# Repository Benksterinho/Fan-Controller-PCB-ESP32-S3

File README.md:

# JumboNAS Fan Controller PCB (ESP32-S3, Rev A)

This repository contains the hardware design and supporting documentation for a maker-friendly 4-wire PWM fan controller board built around ESP32-S3.

The PCB is intended for projects that need to power and control a standard 12 V PC fan, read tach feedback, and optionally show status on an SPI display, with room for future telemetry and expansion.

## What This Board Is For

- Controlling one 12 V 4-wire PWM fan from an ESP32-S3.
- Reading fan tach pulses for RPM measurement.
- Running standalone logic in CircuitPython on ESP32-S3.
- Driving an external ST7789 SPI display header.
- Exposing safe optional GPIOs through an expansion header.

Typical use cases:

- DIY NAS or homelab cooling controller.
- Smart enclosure or cabinet fan controller.
- General embedded fan-control bring-up platform.

## Hardware Overview

- Input power: 19-24 V DC recommended.
- Reverse polarity and surge protection at board input.
- 12 V rail: K7812 SIP module regulator.
- 3.3 V rail: K7803 SIP module regulator.
- Controller: ESP32-S3-WROOM-1-N16R8.
- Fan interface: Intel-style 4-pin PWM fan header.
- Programming/debug: external 1x6 UART header.

Input note:

- 19-24 V is the supported operating range for Rev A.
- 17-18 V may work in some conditions but is not guaranteed with the current Schottky protection stage.

## Project Status

Rev A is an actively developed hardware revision focused on first-pass manufacturability and bring-up reliability.

Current priorities:

- Keep BOM practical for PCBWay/LCSC assembly.
- Keep board size within cost-efficient limits (target under 99 x 99 mm).
- Use conservative, proven power-stage choices for a first hardware spin.

## Repository Layout

- [docs](docs): design rationale, requirements, BOM, sourcing, and build notes.
- [docs/sheet-specs](docs/sheet-specs): per-subsheet intent and signal definitions.
- [hardware/kicad/fan_controller_revA](hardware/kicad/fan_controller_revA): KiCad project files for Rev A.
- [firmware](firmware): reserved area for CircuitPython firmware and bring-up utilities.

## If You Want To Build One

1. Read [docs/requirements.md](docs/requirements.md) for scope and constraints.
2. Read [docs/architecture.md](docs/architecture.md) for system-level decisions.
3. Review [docs/bom-revA.csv](docs/bom-revA.csv) and [docs/bom-revA-status.md](docs/bom-revA-status.md).
4. Open the KiCad project in [hardware/kicad/fan_controller_revA](hardware/kicad/fan_controller_revA).
5. Follow manufacturing notes in [docs/pcbway-assembly.md](docs/pcbway-assembly.md).

## Key Docs

- [docs/architecture.md](docs/architecture.md)
- [docs/requirements.md](docs/requirements.md)
- [docs/current-budget.md](docs/current-budget.md)
- [docs/schematic-plan.md](docs/schematic-plan.md)
- [docs/gpio-map.md](docs/gpio-map.md)
- [docs/bom-revA.csv](docs/bom-revA.csv)
- [docs/bom-revA-status.md](docs/bom-revA-status.md)
- [docs/sourcing-checklist.md](docs/sourcing-checklist.md)
- [docs/pcbway-assembly.md](docs/pcbway-assembly.md)

## Safety And Scope

This is a low-voltage maker hardware project and is provided as-is. Validate thermal behavior, fan startup behavior, and input transient behavior in your own enclosure and power environment before unattended use.

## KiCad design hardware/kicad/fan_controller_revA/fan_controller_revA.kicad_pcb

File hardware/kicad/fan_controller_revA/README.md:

# Fan Controller Rev A - KiCad Notes

Generated schematic files were removed. This folder now serves as the capture guide and naming reference.

## Files

- howto_subsheets/ (step-by-step capture guides)
- pcb_layout/ (subsheet-specific PCB Editor placement and routing guides)
- README.md (capture order and shared net naming)

## Capture Order

1. InputProtection
2. Power12V
3. Power3V3
4. ESP32S3Core
5. Fan4Wire
6. DisplayHeader_ST7789
7. ExternalProgrammingHeader
8. TestPoints
9. OptionalExpansionHeader

## Global Net Names To Reuse

- VIN_PROTECTED
- 12V
- 3V3
- GND
- EN_RESET
- GPIO0_BOOT
- UART_TX
- UART_RX
- FAN_PWM
- FAN_TACH
- SPI_SCK
- SPI_MOSI
- DISP_CS
- DISP_DC
- DISP_RST

## Notes

- Recreate all schematic sheets from docs/sheet-specs/*.md.
- Keep net names aligned with this README to avoid cross-sheet drift.
- Onboard rail telemetry is deferred from Rev A; add it only in a later revision if bring-up shows a real need.

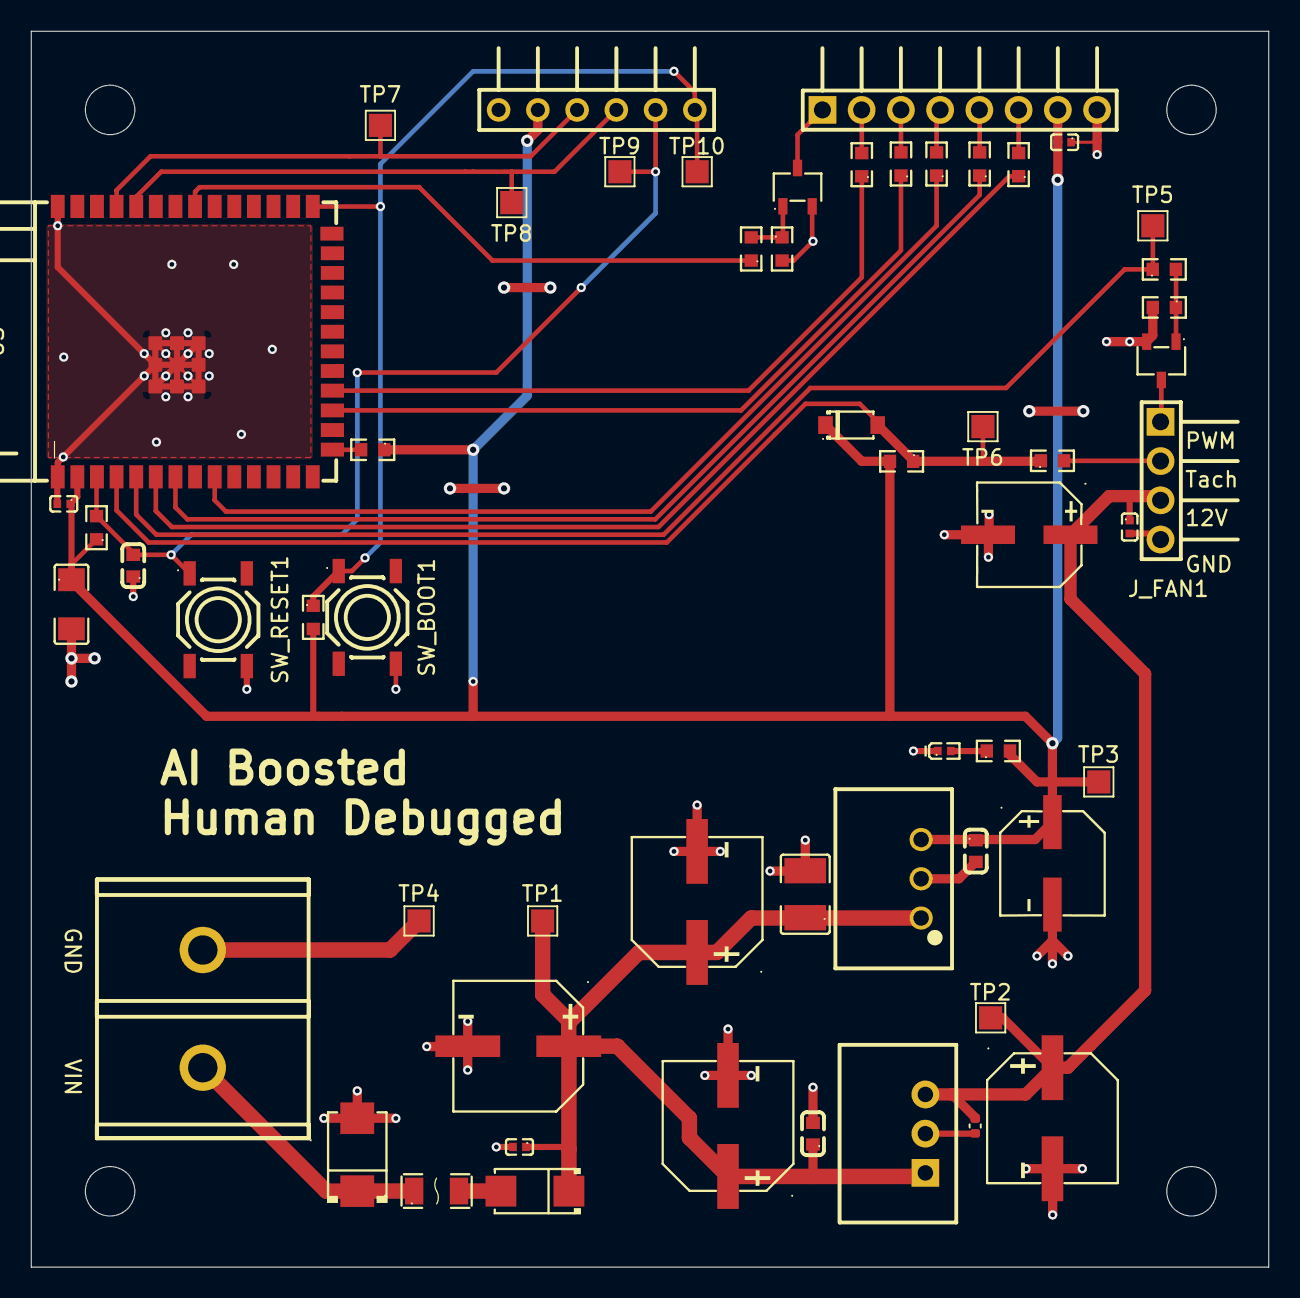
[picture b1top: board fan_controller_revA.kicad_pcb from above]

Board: 2 copper layers, 80.1 x 80.0 mm, 57 parts (0 on the bottom side), 30 nets.

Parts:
C12_IN_BULK1, C33_IN_BULK1: 100uF 50V ±20%; C72480_CAP-SMD_BD8_0-L8_3-W8_3-FD
C12_IN_BYP1: 1uF (105) ±10% 50V; C15849_C0603
C12_OUT_BULK1: 47uF 25V; C72480_CAP-SMD_BD8_0-L8_3-W8_3-FD
C12_OUT_BYP1: 100nF 50V X7R; C_0402_1005Metric
C33_IN_BYP1: CL32A106KBJNNNE; C380537_C1210
C33_OUT_BULK1: RVT100UF16V67RV0016; C2887276_CAP-SMD_BD6_3-L6_6-W6_6-LS7_2-FD
C33_OUT_BYP1: CL10A106MO8NQNC; C92487_C0603
C_BULK1: 22uF（226）±10% 16V; C90146_C1206
C_DEC1: CL05B104KB54PNC; C307331_C0402
C_DISP_VCC1: CL05B104KB54PNC; C307331_C0402
C_EN1: 1uF/50V X7R; C15849_C0603
C_FAN_BULK1: VUA470M1ETR-0607; C3029614_CAP-SMD_BD6_3-L6_6-W6_6-FD
C_FAN_HF1: CL05B104KB54PNC; C307331_C0402
C_IN_BULK1: 100uF 50V ±20%; C72480_CAP-SMD_BD8_0-L8_3-W8_3-FD
C_IN_BYP1: CL05B104KB54PNC; C307331_C0402
D1: SS36; C16015_SMA_L4_3-W2_6-LS5_2-RD
D_TACH_CLAMP1: MBR0520LT1G; C23848_SOD-123_L2_8-W1_8-LS3_7-RD
D_TVS_IN1: SMBJ26A-13-F; C135062_SMB_L4_6-W3_6-LS5_3-RD
F1: 2A 63V; C3105_F1206
J_DISP1: HX PZ2.54-1X8P WZ; C32713267_HDR-TH_8P-P2_54-H-M-W10_3
J_FAN1: HX PZ2.54-1X4P WZ; C32713263_HDR-TH_4P-P2_54-H-M-W10_3
J_PROG1: HX PZ2.54-1X6P WZ-P; C42453955_HDR-TH_6P-P2_54-H-M_DS1022-1X6RUF11-B
J_PWR1: DBT30C-7.62-2P; C395939_CONN-TH_2P-P7_62_DBT30C-7_62-2P
LED_POWER2: FC-F1005UGK-520M5; C130723_LED0402-RD
Q1: MMBT3904_C181119; C181119_SOT-23-3_L2_9-W1_6-P1_90-LS2_8-BR
Q_BL1: MMBT3904_C181119; C181119_SOT-23-3_L2_9-W1_6-P1_90-LS2_8-BR
R_BASE1: 2.2KΩ (2201) ±1%; C4190_R0603
R_BL_BASE1: 2.2KΩ (2201) ±1%; C4190_R0603
R_BL_PD1: 100KΩ (1003) ±1%; C25803_R0603
R_BOOT1: 10KΩ (1002) ±1%; C25804_R0603
R_BPD1: 100KΩ (1003) ±1%; C25803_R0603
R_CS1: FRC0603F33R0TS; C2909394_R0603
R_DC1: FRC0603F33R0TS; C2909394_R0603
R_EN1: 10KΩ (1002) ±1%; C25804_R0603
R_JTAG1: RC0603JR-0710KL; C99198_R0603
R_LED_PWR2: 1KΩ (1001) ±1%; C22548_R0603
R_MOSI1: FRC0603F33R0TS; C2909394_R0603
R_RST3: FRC0603F33R0TS; C2909394_R0603
R_SCK1: FRC0603F33R0TS; C2909394_R0603
R_TACH_PU1: RC0603FR-0710KL; C98220_R0603
R_TACH_SERIES1: 1KΩ (1001) ±1%; C22548_R0603
SW_BOOT1: TL3342F160QG; C2886898_SW-SMD_4P-L5_2-W5_2-P3_70-LS6_4-BL
SW_RESET1: TL3342F160QG; C2886898_SW-SMD_4P-L5_2-W5_2-P3_70-LS6_4-BL
TP1, TP2, TP3, TP4, TP5, TP6, TP7, TP8, TP9, TP10: TestPoint; TestPoint_Pad_1.5x1.5mm
U1: K7812-1000R3_C5369648; C5369648_PWRM-TH_K7812-1000R3
U2: K7803-1000R3_C5369647; C5369647_PWRM-TH_YLPTEC_K78XX-1000R3
U3: ESP32-S3-WROOM-1(N16R8); C2913202_WIRELM-SMD_ESP32-S3-WROOM-1

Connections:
/DisplayHeader_ST7789/3V3: C33_OUT_BULK1.1, C33_OUT_BYP1.1, C_BULK1.1, C_DEC1.1, C_DISP_VCC1.2, D_TACH_CLAMP1.1 (C), J_DISP1.7, J_PROG1.5, R_BOOT1.2, R_EN1.1, R_JTAG1.1, R_LED_PWR2.2, R_TACH_PU1.2, TP3.1 (1_1), U2.3 (+Vo), U3.2 (3V3)
/DisplayHeader_ST7789/BLK_Header: J_DISP1.1, Q_BL1.3
/DisplayHeader_ST7789/DISP_BL: R_BL_BASE1.1, U3.33 (IO40)
/DisplayHeader_ST7789/DISP_CS: R_CS1.1, U3.18 (IO10)
/DisplayHeader_ST7789/DISP_DC: R_DC1.1, U3.17 (IO9)
/DisplayHeader_ST7789/DISP_RST: R_RST3.1, U3.9 (IO16)
/DisplayHeader_ST7789/SPI_MOSI: R_MOSI1.1, U3.7 (IO7)
/DisplayHeader_ST7789/SPI_SCK: R_SCK1.1, U3.6 (IO6)
/ESP32S3Core/EN_RESET: C_EN1.2, J_PROG1.2, R_EN1.2, SW_RESET1.1, TP9.1 (1_1), U3.3 (EN)
/ESP32S3Core/FAN_PWM: R_BASE1.1, TP5.1 (1_1), U3.5 (IO5)
/ESP32S3Core/FAN_TACH: D_TACH_CLAMP1.2 (A), R_TACH_PU1.1, R_TACH_SERIES1.1, TP6.1 (1_1), U3.4 (IO4)
/ESP32S3Core/GPIO0_BOOT: J_PROG1.1, R_BOOT1.1, SW_BOOT1.1, TP10.1 (1_1), U3.27 (IO0)
/ESP32S3Core/UART_RX: J_PROG1.3, TP8.1 (1_1), U3.36 (RXD0)
/ESP32S3Core/UART_TX: J_PROG1.4, TP7.1 (1_1), U3.37 (TXD0)
/Fan4Wire/12V: C12_OUT_BULK1.1, C12_OUT_BYP1.1, C_FAN_BULK1.1, C_FAN_HF1.1, J_FAN1.3, TP2.1 (1_1), U1.3 (+Vo/GND)
/InputProtection/VIN_FUSED: D1.2 (A), F1.2
/InputProtection/VIN_PROTECTED: C12_IN_BULK1.1, C12_IN_BYP1.1, C33_IN_BULK1.1, C33_IN_BYP1.1, C_IN_BULK1.1, C_IN_BYP1.1, D1.1 (K), TP1.1 (1_1), U1.1 (Vin), U2.1 (Vin)
/InputProtection/VIN_RAW: D_TVS_IN1.1 (K), F1.1, J_PWR1.1
GND: C12_IN_BULK1.2, C12_IN_BYP1.2, C12_OUT_BULK1.2, C12_OUT_BYP1.2, C33_IN_BULK1.2, C33_IN_BYP1.2, C33_OUT_BULK1.2, C33_OUT_BYP1.2, C_BULK1.2, C_DEC1.2, C_DISP_VCC1.1, C_EN1.1, C_FAN_BULK1.2, C_FAN_HF1.2, C_IN_BULK1.2, C_IN_BYP1.2, D_TVS_IN1.2 (A), J_DISP1.8, J_FAN1.4, J_PROG1.6, J_PWR1.2, LED_POWER2.1 (K), Q1.2, Q_BL1.2, R_BL_PD1.2, R_BPD1.2, SW_BOOT1.4, SW_RESET1.4, TP4.1 (1_1), U1.2 (GND/-Vo), U2.2 (GND), U3.1 (GND), U3.40 (GND), U3.41 (GND)
unnamed: J_DISP1.2, R_CS1.2
unnamed: J_DISP1.3, R_DC1.2
unnamed: J_DISP1.4, R_RST3.2
unnamed: J_DISP1.5, R_MOSI1.2
unnamed: J_DISP1.6, R_SCK1.2
unnamed: J_FAN1.1, Q1.3
unnamed: J_FAN1.2, R_TACH_SERIES1.2
unnamed: LED_POWER2.2 (A), R_LED_PWR2.1
unnamed: Q1.1, R_BASE1.2, R_BPD1.1
unnamed: Q_BL1.1, R_BL_BASE1.2, R_BL_PD1.1
unnamed: R_JTAG1.2, U3.15 (IO3)

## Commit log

2026-06-09 Initial public release
